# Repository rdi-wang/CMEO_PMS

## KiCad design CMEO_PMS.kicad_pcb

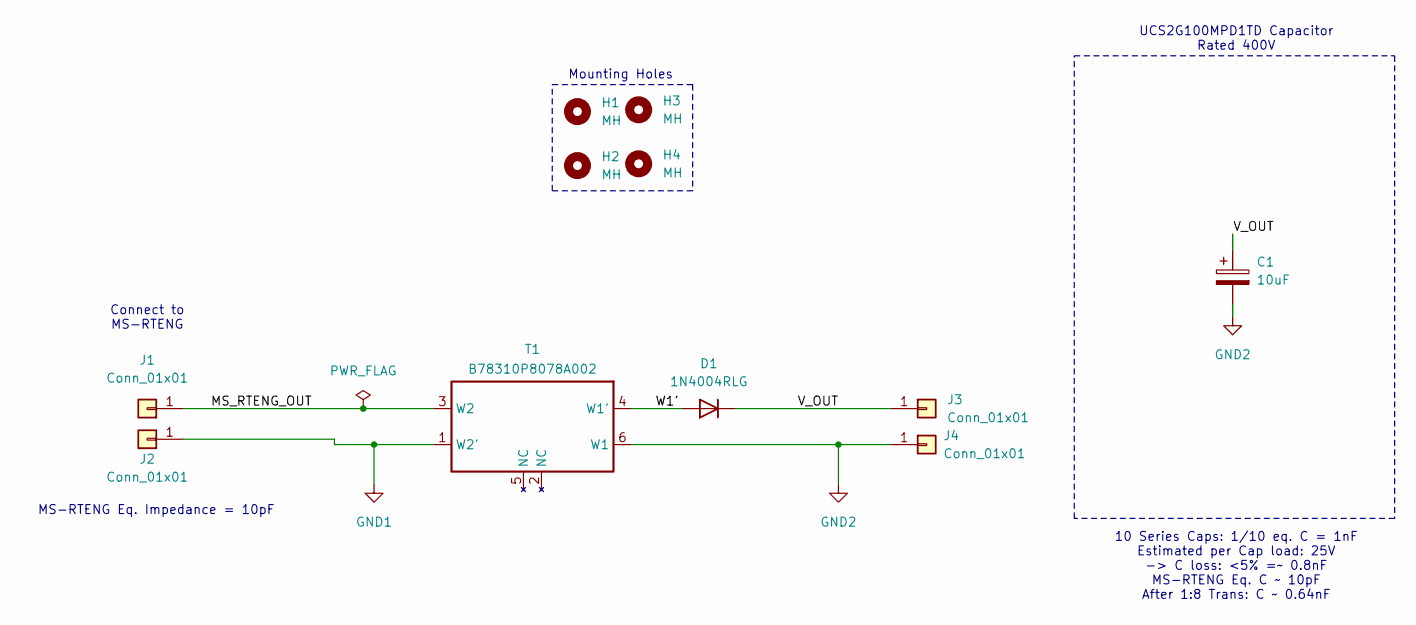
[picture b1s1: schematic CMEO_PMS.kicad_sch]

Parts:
C1: 10uF; CP_Radial_D10.0mm_P5.00mm
D1: 1N4004RLG; D_DO-41_SOD81_P7.62mm_Horizontal
H1, H2, H3, H4: MH; MountingHole_3.2mm_M3
J1, J2, J3, J4: Conn_01x01; PinHeader_1x01_P2.54mm_Vertical
T1: B78310P8078A002

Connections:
/MS_RTENG_OUT: J1.1 (Pin_1_1), T1.3 (W2)
/V_OUT: C1.1, D1.1 (K), J3.1 (Pin_1_1)
/W1': D1.2 (A), T1.4 (W1')
GND1: J2.1 (Pin_1_1), T1.1 (W2')
GND2: C1.2, J4.1 (Pin_1_1), T1.6 (W1)

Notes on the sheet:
Connect to MS-RTENG
10 Series Caps: 1/10 eq. C = 1nF Estimated per Cap load: 25V -> C loss: <5% =~ 0.8nF MS-RTENG Eq. C ~ 10pF After 1:8 Trans: C ~ 0.64nF
UCS2G100MPD1TD Capacitor Rated 400V
Mounting Holes
MS-RTENG Eq. Impedance = 10pF

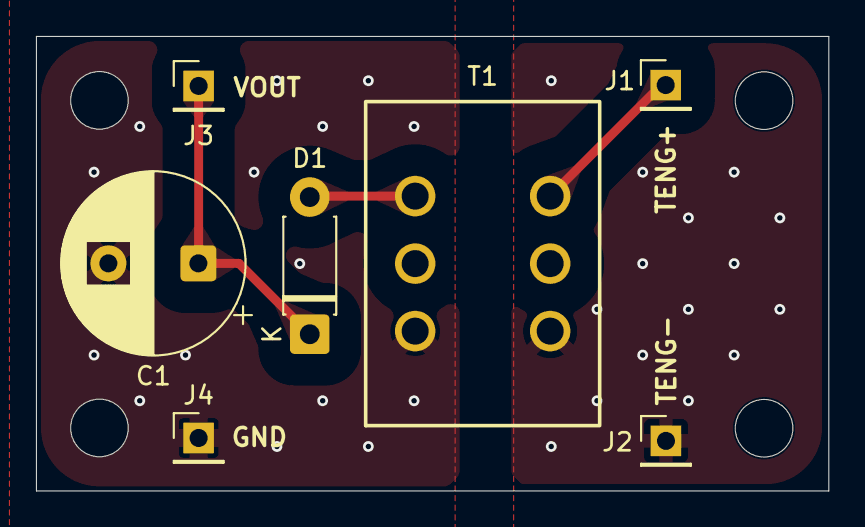
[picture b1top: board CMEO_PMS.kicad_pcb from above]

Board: 2 copper layers, 44.0 x 25.2 mm, 11 parts (0 on the bottom side), 5 nets.

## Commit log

2026-05-18 CMEO_PMS Board V1.0 REV A
    Completed first iteration of CMEO PMS board
2026-05-20 CMEO_PMS Board V1.0 REV B
    - Separated input and output headers to reduce risk of high voltage breakdown
    - Increased fill gap to 2mm to reduce risk of high voltage breakdown
    - Changed diode to THT for easier soldering
    - Changed capacitor to 10uF, 400V limit. increase in capacitance is to better act as a battery for power purposes
2026-05-20 Fixed Silkscreen errors
